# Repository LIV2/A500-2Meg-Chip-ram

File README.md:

# A500/2000 2MB Chip RAM Mod

This is an adapter board to retrofit a 2MB Agnus into an Amiga 500/2000 and also includes 2MB of chip ram

## Assembly Steps
1. Solder the DRAM, U4, U3
2. Solder the Capacitors & Resistor (Only fit VBB capacitor if your Agnus says VBB on the top!)
3. Solder the PLCC Socket making sure that the socket aligns exactly with the outline on the top of the PCB!
4. Solder the PLCC Plug, make sure the orientation matches the silkscreen on the PCB!
5. Make sure that JP2 is set as shown: (A500 only)<br/>

6. Insert the adapter, ensure that the adapter is oriented correctly by checking that the pin 1 marking matches the location on your motherboard<br />

## A20 Connection
### A500
Solder a wire to A20 and connect the other end at one of the following locations:
   * Gary pin 36
   * CPU pin 48
   * JP5 Top left pad (A500 Rev 6)

### A2000
Solder a wire to A20 and connect the other end at one of the following locations:
   * Gary pin 36
   * CPU pin 48
   * Also available from a via next to the power connector as indicated here:  

## Jumper Settings
The default jumper settings do not need to be changed and will work on all systems. 

The multiplexer at U4 is optional, if you decide not to fit this you can cut & set the 28M/MUX jumper to 28M.

Rev 6A Amiga 500's have jumpers that can be used to provide the A20 signal on pin 35 instead of XCLK
This allows us to use this adapter without having to add the wire to A20 but note **this will mean you cannot use a genlock on this Amiga!**

In this case you must set J1 to 28M to bypass the XCLK/28M Mux then set J2 of the adapter to A20<br />
If you wish to do this then you will also need to change the jumper settings at J5 on your A500 motherboard<br />

## Bill of materials
|Component|Location|QTY|Link|Notes|
|---------|--------|---|----|-----|
|Ceramic Capacitor, 0.1uF, 0805|C1-5|5|[Mouser](https://www.mouser.com/ProductDetail/710-885012207098)||
|Ceramic Capacitor, 0.1uF, 0805|C7/VBB|1|[Mouser](https://www.mouser.com/ProductDetail/710-885012207098)|Optional: Fit for VBB Agnus only|
|Ceramic Capacitor, 22pF, 0805|C6|1|[Mouser](https://www.mouser.com/ProductDetail/710-885012007053) ||
|Resistor, 150 Ohm, 0805|R1|1|[Mouser](https://www.mouser.se/ProductDetail/652-CR0805JW-151ELF)||
|74AHC1G08 Single 2-Input AND Gate, SOT-23-5|U3|1|[Mouser](https://www.mouser.com/ProductDetail/595-SN74AHC1G08DBVR)||
|74AHCT158 Quad 2-input Multiplexer, SOIC-16|U4|1|[Mouser](https://www.mouser.com/ProductDetail/595-SN74AHCT158D)|Optional, set J1 to "28M" to bypass|
|PLCC-84 Socket, SMD|U1|1|[Mouser](https://www.mouser.com/ProductDetail/517-8484-21B1-RK-TP)||
|PLCC-84 SMD Plug||1|[jbilanders PLCC-84 Plug](https://github.com/jbilander/PLCC-84-plug)<br>[Adapt-Plus](https://www.adapt-plus.com/products_html/apw9328-zc160.html)<br>[RS-Components](https://uk.rs-online.com/web/p/ic-socket-adapters/7419684/)||
|5V, 1Mx16 EDO/FPM DRAM, SOJ-42<br>- K4F151611<br>- K4E151611<br>- GM71C18163C<br>- AS4C1M16E5|U2|1|eBay, Aliexpress etc||

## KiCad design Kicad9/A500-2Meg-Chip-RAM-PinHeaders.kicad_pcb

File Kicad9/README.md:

# Kicad Version

The project has been migrated to Kicad with some small changes
* All SMD parts (except the RAM) were moved to the bottom side.
* Added a single gate option for U4.
* VBB option was implemented as a solder jumper. This makes it possible to switch without removing the whole adapter from the motherboard.

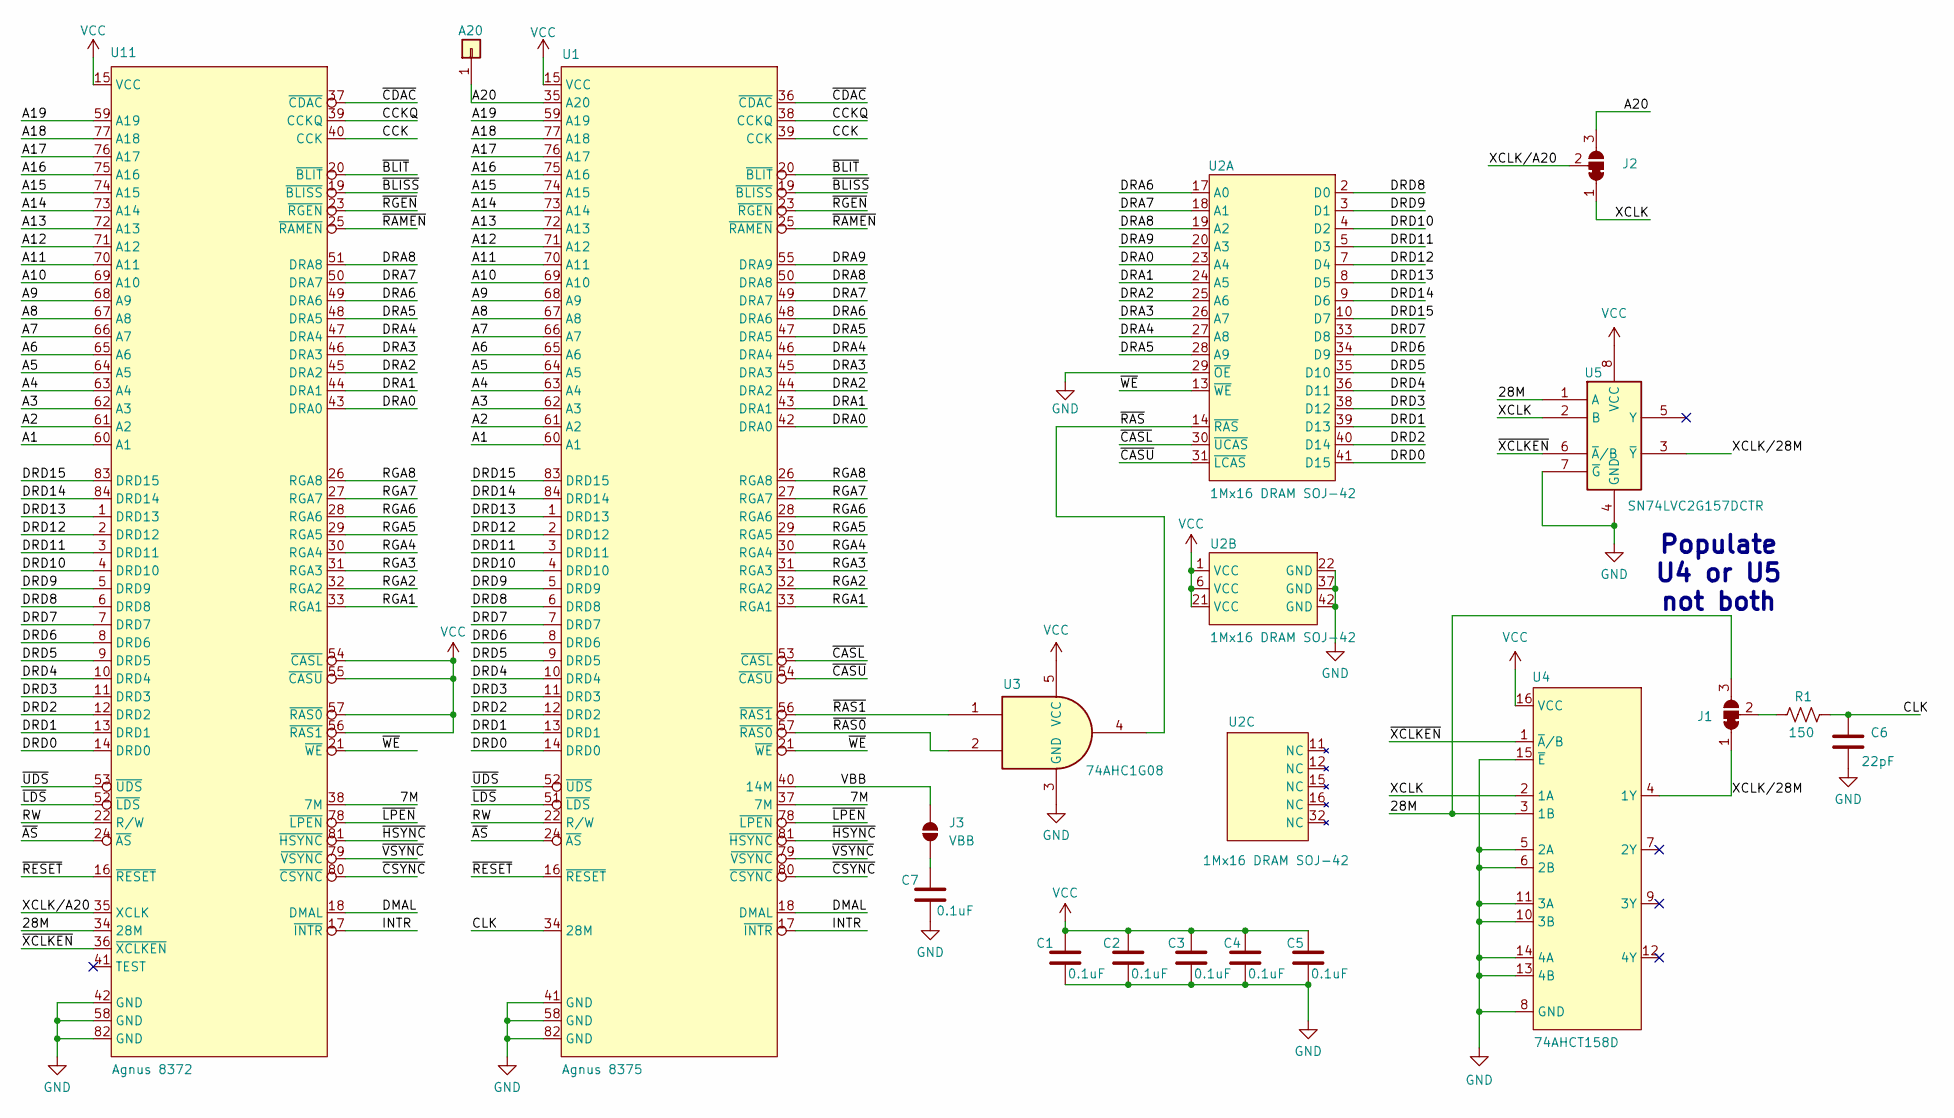
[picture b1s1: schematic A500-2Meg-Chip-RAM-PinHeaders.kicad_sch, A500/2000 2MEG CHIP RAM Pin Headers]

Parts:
A20: A20; PinHeader_1x01_P2.54mm_Horizontal
C1, C2, C3, C4, C5, C7: 0.1uF; C_0805_2012Metric_Pad1.18x1.45mm_HandSolder; LCSC C28233
C6: 22pF; C_0805_2012Metric_Pad1.18x1.45mm_HandSolder; LCSC C1804
J1, J2: H1; SolderJumper-3_P1.3mm_Bridged12_Pad1.0x1.5mm
J3: VBB; SolderJumper-2_P1.3mm_Open_RoundedPad1.0x1.5mm
R1: 150; R_0805_2012Metric_Pad1.20x1.40mm_HandSolder; LCSC C17471
U1: Agnus 8375
U2: 1Mx16 DRAM SOJ-42; SOJ42
U3: 74AHC1G08; SOT-23-5_HandSoldering; LCSC C7467
U4: 74AHCT158D; JEITA_SOIC-16_3.9x9.9mm_P1.27mm; LCSC C2865242
U5: SN74LVC2G157DCTR; SSOP-8_2.95x2.8mm_P0.65mm; LCSC C78048
U11: Agnus 8372; Agnus 8372A

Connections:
/7M: U1.37 (7M), U11.38 (7M)
/28M: J1.3 (B), U4.3 (1B), U5.1 (A), U11.34 (28M)
/A1: U1.60 (A1), U11.60 (A1)
/A2: U1.61 (A2), U11.61 (A2)
/A3: U1.62 (A3), U11.62 (A3)
/A4: U1.63 (A4), U11.63 (A4)
/A5: U1.64 (A5), U11.64 (A5)
/A6: U1.65 (A6), U11.65 (A6)
/A7: U1.66 (A7), U11.66 (A7)
/A8: U1.67 (A8), U11.67 (A8)
/A9: U1.68 (A9), U11.68 (A9)
/A10: U1.69 (A10), U11.69 (A10)
/A11: U1.70 (A11), U11.70 (A11)
/A12: U1.71 (A12), U11.71 (A12)
/A13: U1.72 (A13), U11.72 (A13)
/A14: U1.73 (A14), U11.73 (A14)
/A15: U1.74 (A15), U11.74 (A15)
/A16: U1.75 (A16), U11.75 (A16)
/A17: U1.76 (A17), U11.76 (A17)
/A18: U1.77 (A18), U11.77 (A18)
/A19: U1.59 (A19), U11.59 (A19)
/A20: A20.1, J2.3 (B), U1.35 (A20)
/CCK: U1.39 (CCK), U11.40 (CCK)
/CCKQ: U1.38 (CCKQ), U11.39 (CCKQ)
/CLK: C6.2, R1.2, U1.34 (28M)
/DMAL: U1.18 (DMAL), U11.18 (DMAL)
/DRA0: U1.42 (DRA0), U2.23 (A4), U11.43 (DRA0)
/DRA1: U1.43 (DRA1), U2.24 (A5), U11.44 (DRA1)
/DRA2: U1.44 (DRA2), U2.25 (A6), U11.45 (DRA2)
/DRA3: U1.45 (DRA3), U2.26 (A7), U11.46 (DRA3)
/DRA4: U1.46 (DRA4), U2.27 (A8), U11.47 (DRA4)
/DRA5: U1.47 (DRA5), U2.28 (A9), U11.48 (DRA5)
/DRA6: U1.48 (DRA6), U2.17 (A0), U11.49 (DRA6)
/DRA7: U1.49 (DRA7), U2.18 (A1), U11.50 (DRA7)
/DRA8: U1.50 (DRA8), U2.19 (A2), U11.51 (DRA8)
/DRA9: U1.55 (DRA9), U2.20 (A3)
/DRD0: U1.14 (DRD0), U2.41 (D15), U11.14 (DRD0)
/DRD1: U1.13 (DRD1), U2.39 (D13), U11.13 (DRD1)
/DRD2: U1.12 (DRD2), U2.40 (D14), U11.12 (DRD2)
/DRD3: U1.11 (DRD3), U2.38 (D12), U11.11 (DRD3)
/DRD4: U1.10 (DRD4), U2.36 (D11), U11.10 (DRD4)
/DRD5: U1.9 (DRD5), U2.35 (D10), U11.9 (DRD5)
/DRD6: U1.8 (DRD6), U2.34 (D9), U11.8 (DRD6)
/DRD7: U1.7 (DRD7), U2.33 (D8), U11.7 (DRD7)
/DRD8: U1.6 (DRD8), U2.2 (D0), U11.6 (DRD8)
/DRD9: U1.5 (DRD9), U2.3 (D1), U11.5 (DRD9)
/DRD10: U1.4 (DRD10), U2.4 (D2), U11.4 (DRD10)
/DRD11: U1.3 (DRD11), U2.5 (D3), U11.3 (DRD11)
/DRD12: U1.2 (DRD12), U2.7 (D4), U11.2 (DRD12)
/DRD13: U1.1 (DRD13), U2.8 (D5), U11.1 (DRD13)
/DRD14: U1.84 (DRD14), U2.9 (D6), U11.84 (DRD14)
/DRD15: U1.83 (DRD15), U2.10 (D7), U11.83 (DRD15)
/INTR: U1.17 (~INTR), U11.17 (~INTR)
/RGA1: U1.33 (RGA1), U11.33 (RGA1)
/RGA2: U1.32 (RGA2), U11.32 (RGA2)
/RGA3: U1.31 (RGA3), U11.31 (RGA3)
/RGA4: U1.30 (RGA4), U11.30 (RGA4)
/RGA5: U1.29 (RGA5), U11.29 (RGA5)
/RGA6: U1.28 (RGA6), U11.28 (RGA6)
/RGA7: U1.27 (RGA7), U11.27 (RGA7)
/RGA8: U1.26 (RGA8), U11.26 (RGA8)
/RW: U1.22 (R/W), U11.22 (R/W)
/VBB: J3.2 (B), U1.40 (14M)
/XCLK: J2.1 (A), U4.2 (1A), U5.2 (B)
/XCLK/28M: J1.1 (A), U4.4 (1Y), U5.3 (~Y)
/XCLK/A20: J2.2 (C), U11.35 (XCLK)
/~AS: U1.24 (~AS), U11.24 (~AS)
/~BLISS: U1.19 (~BLISS), U11.19 (~BLISS)
/~BLIT: U1.20 (~BLIT), U11.20 (~BLIT)
/~CASL: U1.53 (~CASL), U2.30 (~UCAS)
/~CASU: U1.54 (~CASU), U2.31 (~LCAS)
/~CDAC: U1.36 (~CDAC), U11.37 (~CDAC)
/~CSYNC: U1.80 (~CSYNC), U11.80 (~CSYNC)
/~HSYNC: U1.81 (~HSYNC), U11.81 (~HSYNC)
/~LDS: U1.51 (~LDS), U11.52 (~LDS)
/~LPEN: U1.78 (~LPEN), U11.78 (~LPEN)
/~RAMEN: U1.25 (~RAMEN), U11.25 (~RAMEN)
/~RAS0: U1.57 (~RAS0), U3.2
/~RAS1: U1.56 (~RAS1), U3.1
/~RAS: U2.14 (~RAS), U3.4
/~RESET: U1.16 (~RESET), U11.16 (~RESET)
/~RGEN: U1.23 (~RGEN), U11.23 (~RGEN)
/~UDS: U1.52 (~UDS), U11.53 (~UDS)
/~VSYNC: U1.79 (~VSYNC), U11.79 (~VSYNC)
/~WE: U1.21 (~WE), U2.13 (~WE), U11.21 (~WE)
/~XCLKEN: U4.1 (~A/B), U5.6 (~A/B), U11.36 (~XCLKEN)
GND: C1.1, C2.1, C3.1, C4.1, C5.1, C6.1, C7.1, U1.41 (GND), U1.58 (GND), U1.82 (GND), U2.22 (GND), U2.29 (~OE), U2.37 (GND), U2.42 (GND), U3.3 (GND), U4.5 (2A), U4.6 (2B), U4.8 (GND), U4.10 (3B), U4.11 (3A), U4.13 (4B), U4.14 (4A), U4.15 (~E), U5.4 (GND), U5.7 (~G), U11.42 (GND), U11.58 (GND), U11.82 (GND)
unnamed: J1.2 (C), R1.1
unnamed: C7.2, J3.1 (A)
VCC: C1.2, C2.2, C3.2, C4.2, C5.2, U1.15 (VCC), U2.1 (VCC), U2.6 (VCC), U2.21 (VCC), U3.5 (VCC), U4.16 (VCC), U5.8 (VCC), U11.15 (VCC), U11.54 (~CASL), U11.55 (~CASU), U11.56 (~RAS1), U11.57 (~RAS0)

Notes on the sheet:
Populate U4 or U5 not both

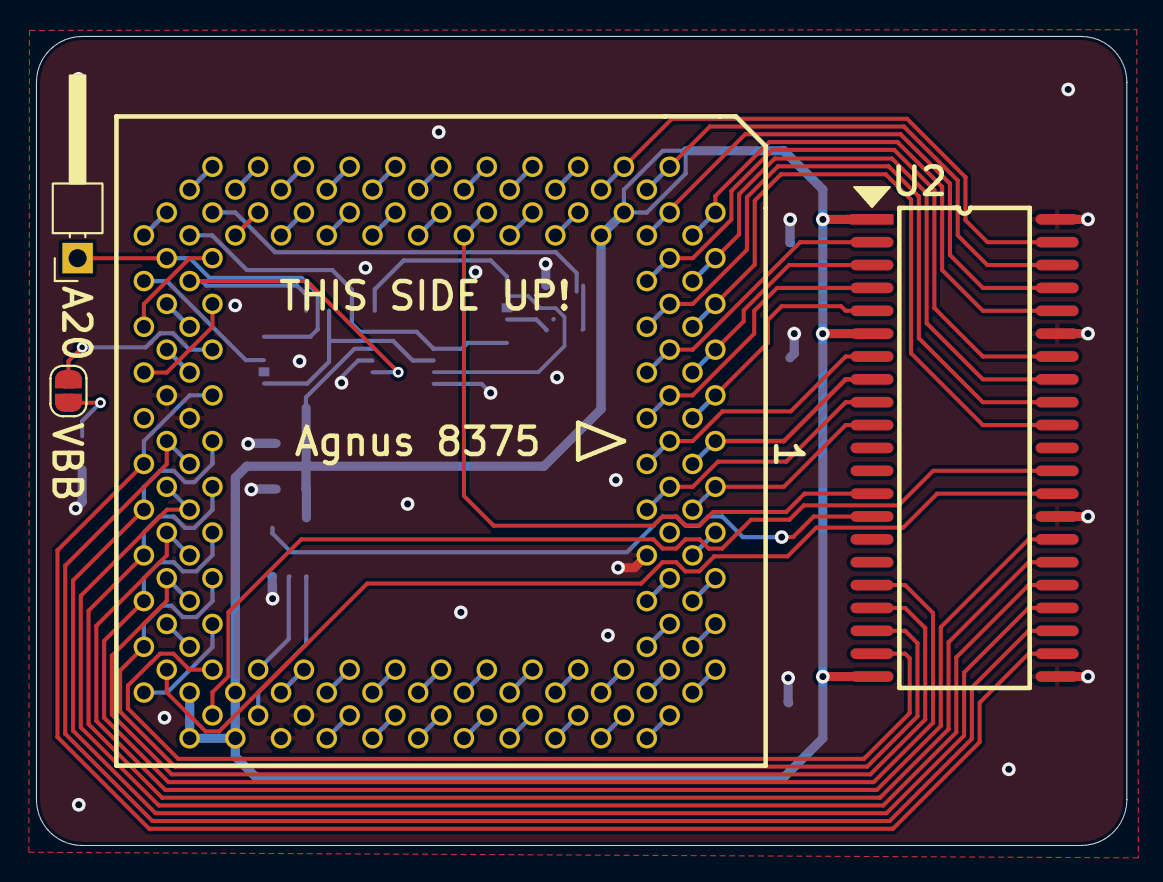
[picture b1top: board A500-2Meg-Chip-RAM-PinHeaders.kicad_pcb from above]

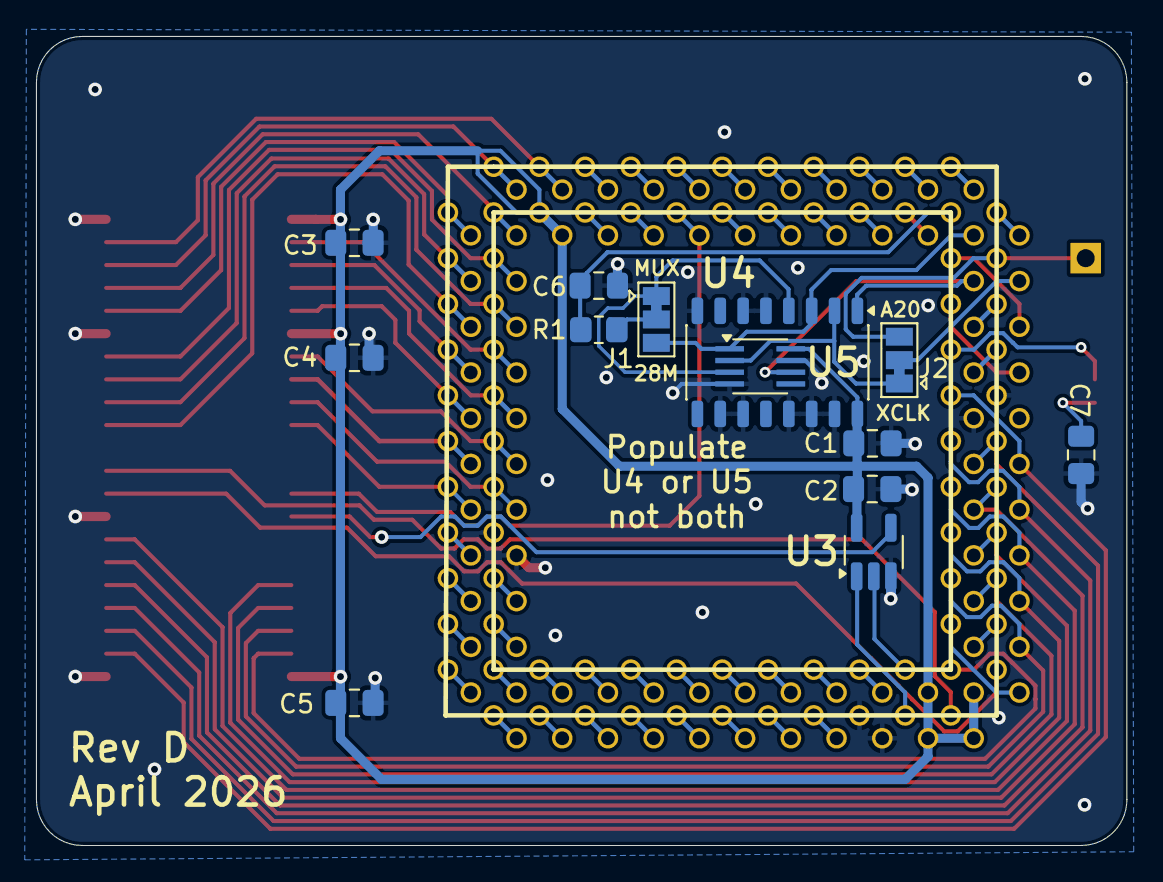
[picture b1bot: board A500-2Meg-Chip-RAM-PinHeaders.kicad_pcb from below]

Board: 2 copper layers, 60.6 x 44.9 mm, 18 parts (13 on the bottom side), 90 nets.

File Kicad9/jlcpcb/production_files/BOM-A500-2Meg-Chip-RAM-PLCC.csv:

Comment,Designator,Footprint,LCSC,Quantity
0.1uF,"C1,C2,C3,C4,C5,C7",C_0805_2012Metric_Pad1.18x1.45mm_HandSolder,C28233,6
150,R1,R_0805_2012Metric_Pad1.20x1.40mm_HandSolder,C17471,1
22pF,C6,C_0805_2012Metric_Pad1.18x1.45mm_HandSolder,C1804,1
74AHC1G08,U3,SOT-23-5_HandSoldering,C7467,1
74AHCT158D,U4,JEITA_SOIC-16_3.9x9.9mm_P1.27mm,C2865242,1
SN74LVC2G157DCTR,U5,SSOP-8_2.95x2.8mm_P0.65mm,C78048,1
Agnus 8375,U1,PLCC-84,,1
A20,A20,PinHeader_1x01_P2.54mm_Horizontal,,1
1Mx16 DRAM SOJ-42,U2,SOJ42,,1
Agnus 8372,U11,PLCC-84_Plug_P1.27mm_mirrored,,1

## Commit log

2020-09-13 Add assembly steps, correct BOM
2020-09-13 Schematic: Update part number for U4
2020-09-13 Fixup my bad spelling in the README
2020-09-18 Move Drill files to Gerber directory
2021-06-13 PLCC Version
2021-06-13 Add message pointing to PLCC version
2021-06-14 Helps to update the gerbers...
2021-06-17 Update README.md
    Fix up jumper comment
2021-10-17 Add some A2000 info to README
2021-10-17 Add A2000 info to README
2021-10-17 Add link to jbilander's awesome PLCC Plug
2022-06-29 Add info for A1000 Rejuvinator users
2023-04-09 Fixup BOM
    VBB cap was mixed in with other 0.1uF capacitors
    VBB cap was also labelled as C7 in the BOM
    Thanks to Stefan Reinauer for pointing this out
2026-05-14 Added Kicad version
2026-05-14 Update README.md for Kicad version
2026-05-14 Add PDF schematics for Kicad version
2026-05-14 Add Kicad version
